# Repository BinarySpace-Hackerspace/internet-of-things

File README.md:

# internet-of-things
Various code for "Internet of Things" Project - January 2015

Project Page: http://www.binaryspace.co.za/wiki/index.php?title=Monthly_Project_January_2015

Current Base Station Examples:

Simple Launchpad

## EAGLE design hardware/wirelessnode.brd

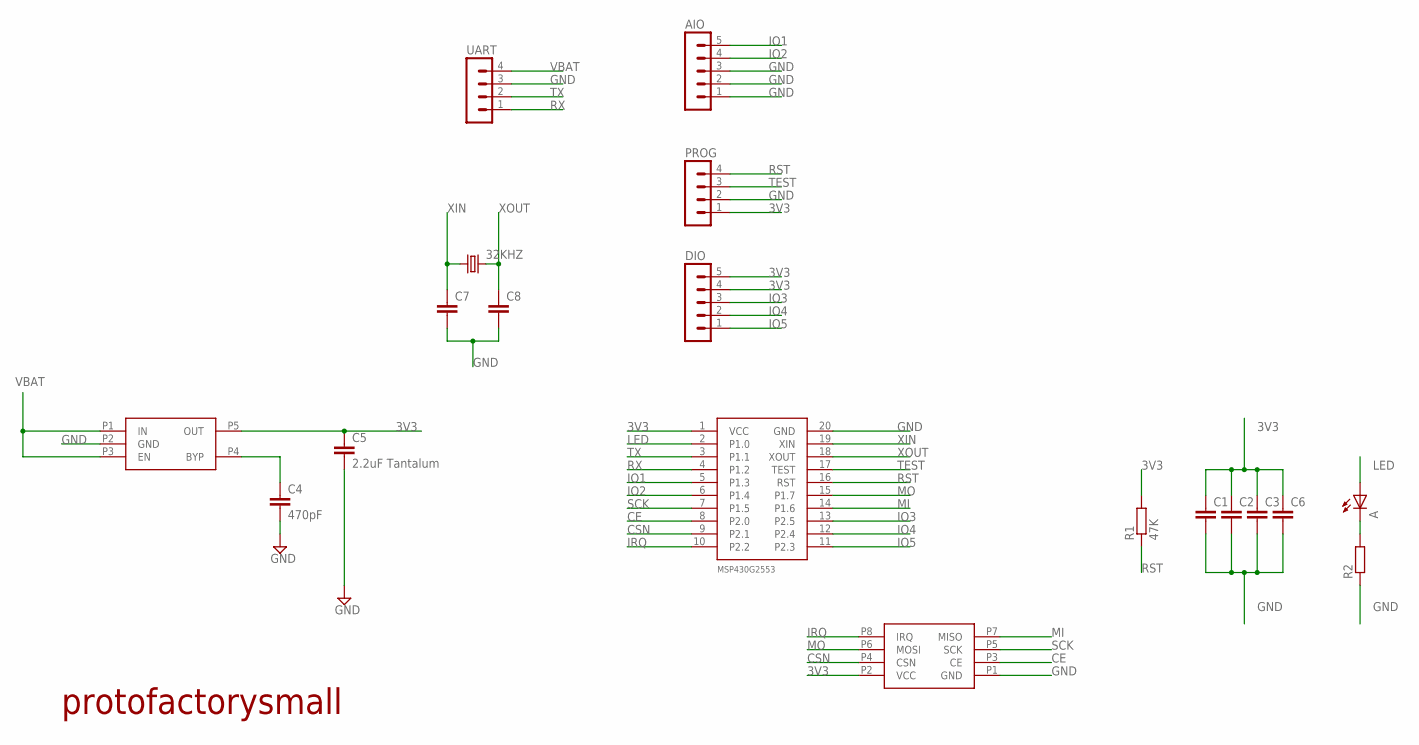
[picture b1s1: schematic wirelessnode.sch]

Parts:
32KHZ: CRYSTALTC26H; TC26H
A: LEDSML0603; SML0603
AIO: MA05-1
C1, C2, C3, C6, C7, C8: C-EUC0603; C0603
C4: 470pF; C0603
C5: 2.2uF Tantalum; C3225
DIO: MA05-1
MSP430G2553: MSP430G2553_20PINMSP430G2553; DIL20
PROG: MA04-1
R1: 47K; R0603
R2: R-EU_R0603; R0603
RF: NRF24L01NRF24L01; NRF24L01
U$1: SMALLPROTOLOGOLOGO; LOGO_SMALL
U$3: MIC5219-X.XBM5MIC5219-3.3YM5TR; SOT-23-5
UART: MA04-1

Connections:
3V3: C1.1, C2.1, C3.1, C5.1, C6.1, DIO.4, DIO.5, MSP430G2553.1 (VCC), PROG.1, R1.2, RF.P2 (VCC), U$3.P5 (OUT)
CE: MSP430G2553.8 (P2.0), RF.P3 (CE)
CSN: MSP430G2553.9 (P2.1), RF.P4 (CSN)
GND: AIO.1, AIO.2, AIO.3, C1.2, C2.2, C3.2, C4.2, C5.2, C6.2, C7.2, C8.2, MSP430G2553.20 (GND), PROG.2, R2.1, RF.P1 (GND), U$3.P2 (GND), UART.3
IO1: AIO.5, MSP430G2553.5 (P1.3)
IO2: AIO.4, MSP430G2553.6 (P1.4)
IO3: DIO.3, MSP430G2553.13 (P2.5)
IO4: DIO.2, MSP430G2553.12 (P2.4)
IO5: DIO.1, MSP430G2553.11 (P2.3)
IRQ: MSP430G2553.10 (P2.2), RF.P8 (IRQ)
LED: A.A, MSP430G2553.2 (P1.0)
MI: MSP430G2553.14 (P1.6), RF.P7 (MISO)
MO: MSP430G2553.15 (P1.7), RF.P6 (MOSI)
unnamed: A.C, R2.2
unnamed: C4.1, U$3.P4 (BYP)
RST: MSP430G2553.16 (RST), PROG.4, R1.1
RX: MSP430G2553.4 (P1.2), UART.1
SCK: MSP430G2553.7 (P1.5), RF.P5 (SCK)
TEST: MSP430G2553.17 (TEST), PROG.3
TX: MSP430G2553.3 (P1.1), UART.2
VBAT: U$3.P1 (IN), U$3.P3 (EN), UART.4
XIN: 32KHZ.1, C7.1, MSP430G2553.19 (XIN)
XOUT: 32KHZ.2, C8.1, MSP430G2553.18 (XOUT)

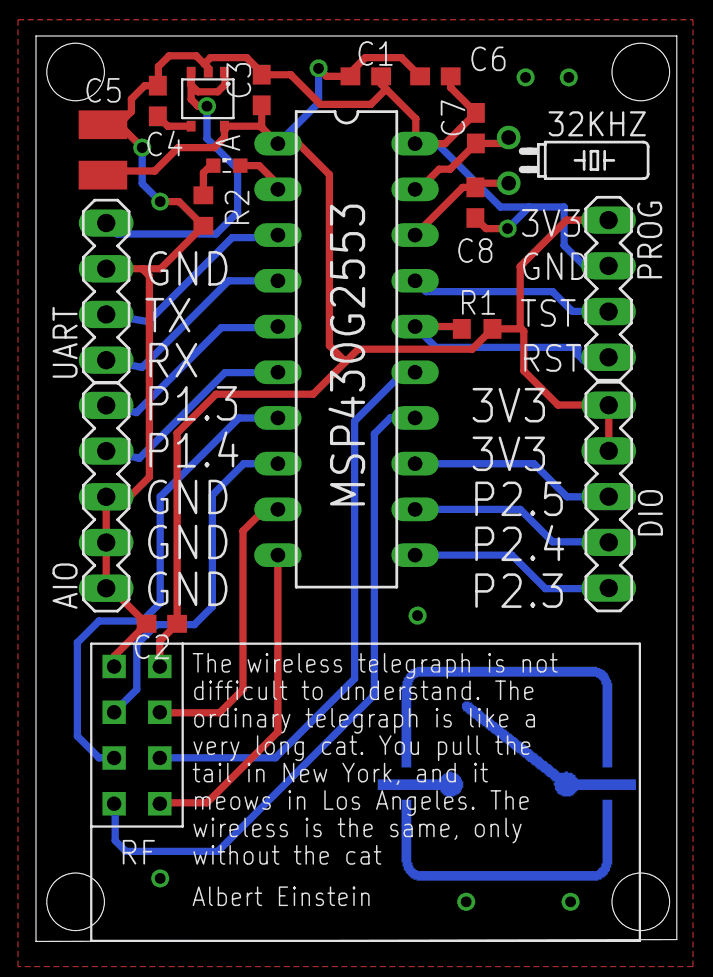
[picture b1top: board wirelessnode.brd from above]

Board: 2 copper layers, 35.6 x 50.3 mm, 20 parts (1 on the bottom side), 23 nets.

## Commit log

2015-01-20 add simple launchpad basestation
2015-01-23 added hardware schematic and pcb layout
